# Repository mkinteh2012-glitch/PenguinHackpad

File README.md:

# PenguinHackpad
This was built by @penguinmo for hackclub
I built this because it seems really cools and it's a project i've never done before
# Images

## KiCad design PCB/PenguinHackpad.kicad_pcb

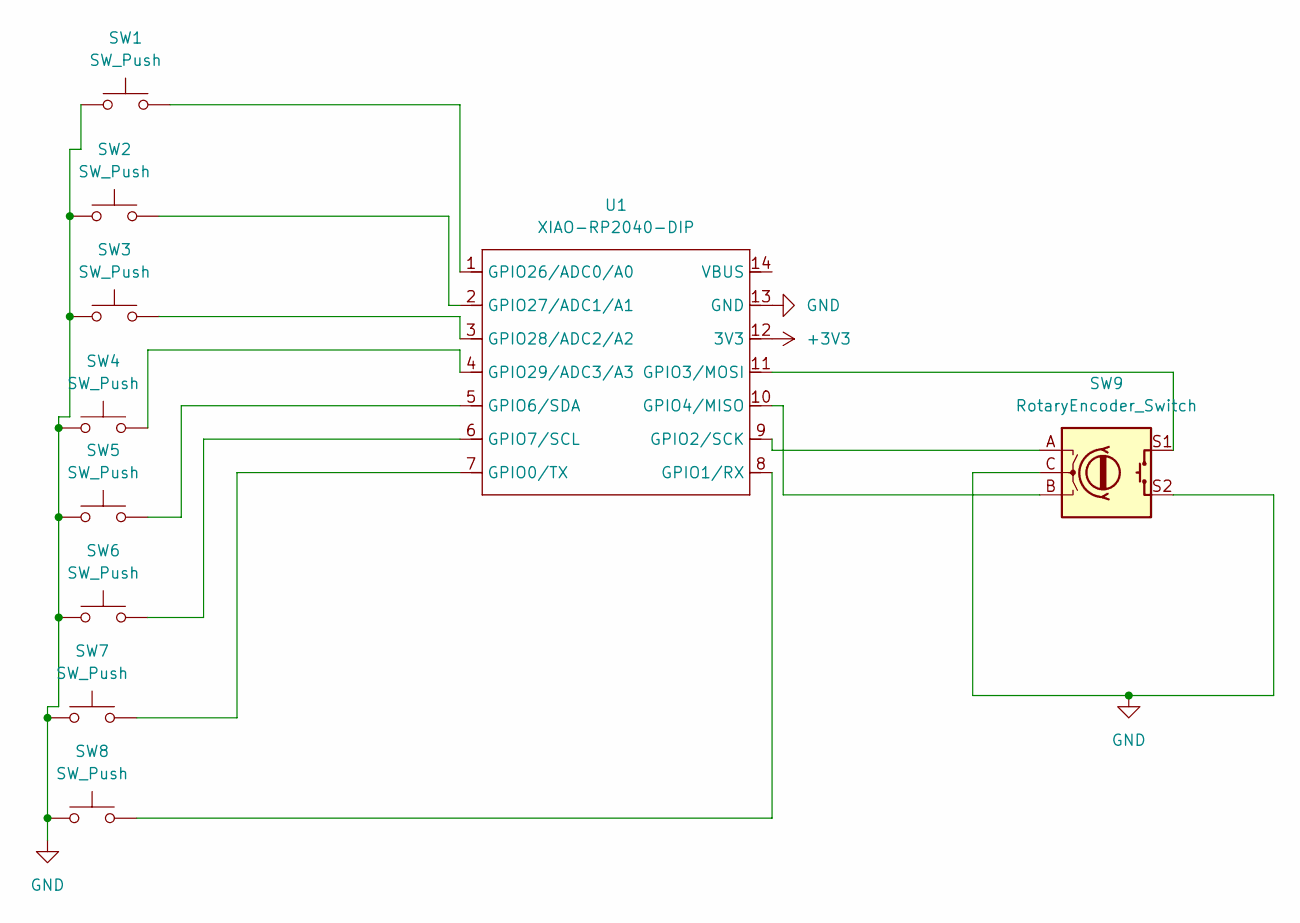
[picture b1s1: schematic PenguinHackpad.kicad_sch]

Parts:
SW1, SW2, SW3, SW4, SW5, SW6, SW7, SW8: SW_Push; SW_Cherry_MX_1.00u_PCB
SW9: RotaryEncoder_Switch; RotaryEncoder_Alps_EC11E-Switch_Vertical_H20mm
U1: XIAO-RP2040-DIP

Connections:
+3V3: U1.12 (3V3)
GND: SW1.1, SW2.1, SW3.1, SW4.1, SW5.1, SW6.1, SW7.1, SW8.1, SW9.C, SW9.S2, U1.13 (GND)
unnamed: SW7.2, U1.7 (GPIO0/TX)
unnamed: SW8.2, U1.8 (GPIO1/RX)
unnamed: SW9.A, U1.9 (GPIO2/SCK)
unnamed: SW9.S1, U1.11 (GPIO3/MOSI)
unnamed: SW9.B, U1.10 (GPIO4/MISO)
unnamed: SW5.2, U1.5 (GPIO6/SDA)
unnamed: SW6.2, U1.6 (GPIO7/SCL)
unnamed: SW1.2, U1.1 (GPIO26/ADC0/A0)
unnamed: SW2.2, U1.2 (GPIO27/ADC1/A1)
unnamed: SW3.2, U1.3 (GPIO28/ADC2/A2)
unnamed: SW4.2, U1.4 (GPIO29/ADC3/A3)

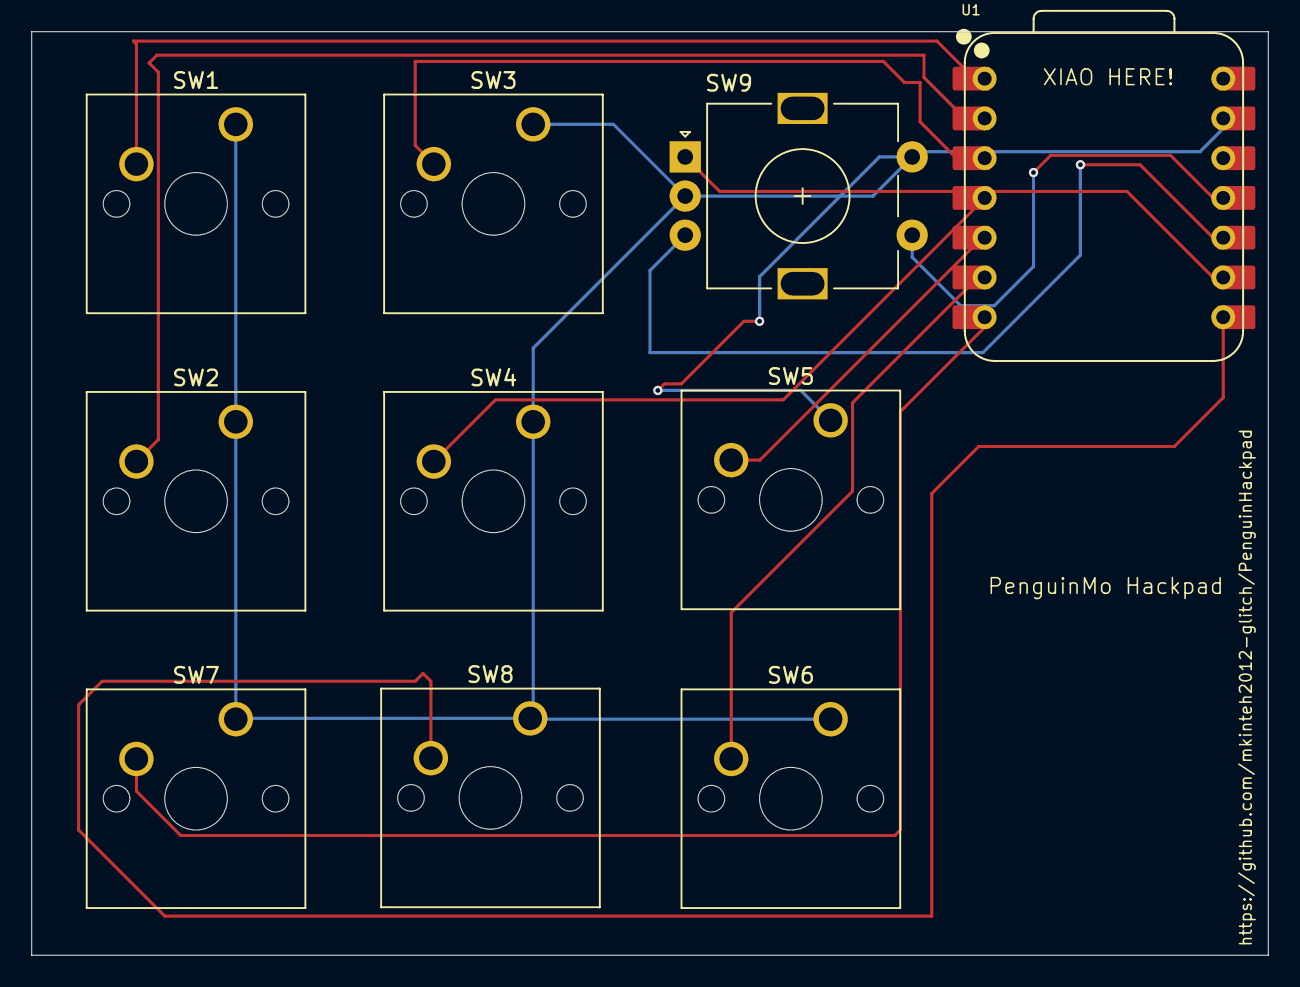
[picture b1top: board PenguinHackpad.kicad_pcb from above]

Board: 2 copper layers, 79.0 x 59.0 mm, 10 parts (0 on the bottom side), 12 nets.

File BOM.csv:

"Id";"Designator";"Footprint";"Quantity";"Designation";"Supplier and ref";
1;"SW2,SW8,SW7,SW6,SW3,SW4,SW5,SW1";"SW_Cherry_MX_1.00u_PCB";8;"SW_Push";;;
2;"U1";"XIAO-RP2040-DIP";1;"XIAO-RP2040-DIP";;;
3;"SW9";"RotaryEncoder_Alps_EC11E-Switch_Vertical_H20mm";1;"RotaryEncoder_Switch";;;

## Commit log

2025-12-31 Create PLACEHOLDER
2025-12-31 Add Hackpad_Bottom.step file
2025-12-31 Update README with project details and images
    Added project description and images to README.
2025-12-31 Update main.py
    Added functionality for RGB color fading on key press.
2025-12-31 ADDED A BOM
2025-12-31 Rename penguin-s-hackpad-journal.md to journal.md
2026-01-01 Add new images to README
    Added two new images to the README file.
